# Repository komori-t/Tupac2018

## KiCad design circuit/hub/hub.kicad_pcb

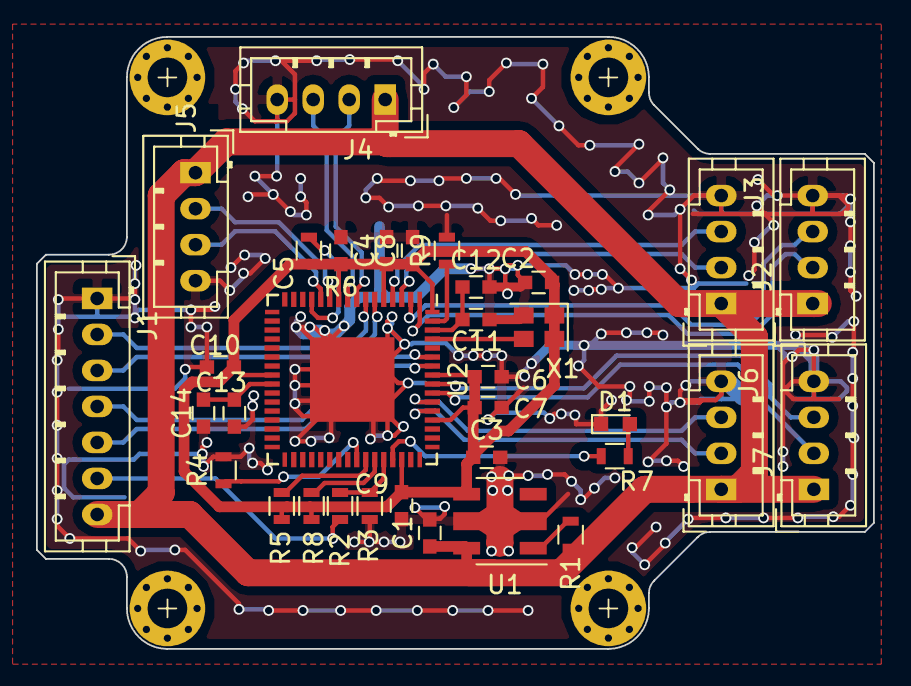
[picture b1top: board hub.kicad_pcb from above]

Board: 2 copper layers, 46.5 x 34.0 mm, 34 parts (0 on the bottom side), 32 nets.

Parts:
C1: 0.33u; C_0603
C2: 0.01u; C_0603
C3: 2.2u; C_0603
C4, C5, C6, C7, C8, C9, C10, C11, C13: 0.1u; C_0603
C12, C14: 1.0u; C_0603
D1: LED; LED_0603
J1: Host-IMU; JST_PH_B7B-PH-K_07x2.00mm_Straight
J2: Dev1; JST_PH_B4B-PH-K_04x2.00mm_Straight
J3: Dev2; JST_PH_B4B-PH-K_04x2.00mm_Straight
J4: Dev4; JST_PH_B4B-PH-K_04x2.00mm_Straight
J5: Dev5; JST_PH_B4B-PH-K_04x2.00mm_Straight
J6: Dev6; JST_PH_B4B-PH-K_04x2.00mm_Straight
J7: Dev7; JST_PH_B4B-PH-K_04x2.00mm_Straight
R1: 2k; R_0603
R2, R3, R4, R5, R6, R8: 100k; R_0603
R7: 1k; R_0603
R9: 12k; R_0603
U1: NJM2884U1-33; SOT-89-5_Housing
U2: USB2517; QFN-64-USB2517
X1: SG-210STF; Oscillator_SMD_SeikoEpson_SG210-4pin_2.5x2.0mm

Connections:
+3V3: C2.1, C3.1, C4.1, C5.1, C6.1, C7.1, C8.1, C9.1, C10.1, R5.2, R6.2, R8.2, U1.4, U2.5, U2.10, U2.24, U2.46, U2.52, U2.57, U2.64, X1.1, X1.4
+5V: C1.1, J1.7, J2.1, J3.1, J4.1, J5.1, J6.1, J7.1, R1.1, U1.5
/Clock: U2.61, X1.3
/Dev1D+: J2.3, U2.2
/Dev1D-: J2.2, U2.1
/Dev2D+: J3.3, U2.4
/Dev2D-: J3.2, U2.3
/Dev3D+: J1.2, U2.7
/Dev3D-: J1.3, U2.6
/Dev4D+: J4.3, U2.9
/Dev4D-: J4.2, U2.8
/Dev5D+: J5.3, U2.12
/Dev5D-: J5.2, U2.11
/Dev6D+: J6.3, U2.54
/Dev6D-: J6.2, U2.53
/Dev7D+: J7.3, U2.56
/Dev7D-: J7.2, U2.55
/HostD+: J1.4, U2.59
/HostD-: J1.5, U2.58
GND: C1.2, C2.2, C3.2, C4.2, C5.2, C6.2, C7.2, C8.2, C9.2, C10.2, C11.2, C12.2, C13.2, C14.2, D1.1, J1.1, J2.4, J3.4, J4.4, J5.4, J6.4, J7.4, R3.2, R4.2, R9.2, U1.2, U2.65, X1.2
unnamed: C11.1, C12.1, U2.62
unnamed: C13.1, C14.1, U2.25
unnamed: D1.2, R7.2
unnamed: R1.2, U1.1
unnamed: R2.2, R3.1, U2.44
unnamed: R4.1, U2.41
unnamed: R5.1, U2.42
unnamed: R6.1, U2.13
unnamed: R7.1, U2.45
unnamed: R8.1, U2.43
unnamed: R9.1, U2.63
VBUS: J1.6, R2.1

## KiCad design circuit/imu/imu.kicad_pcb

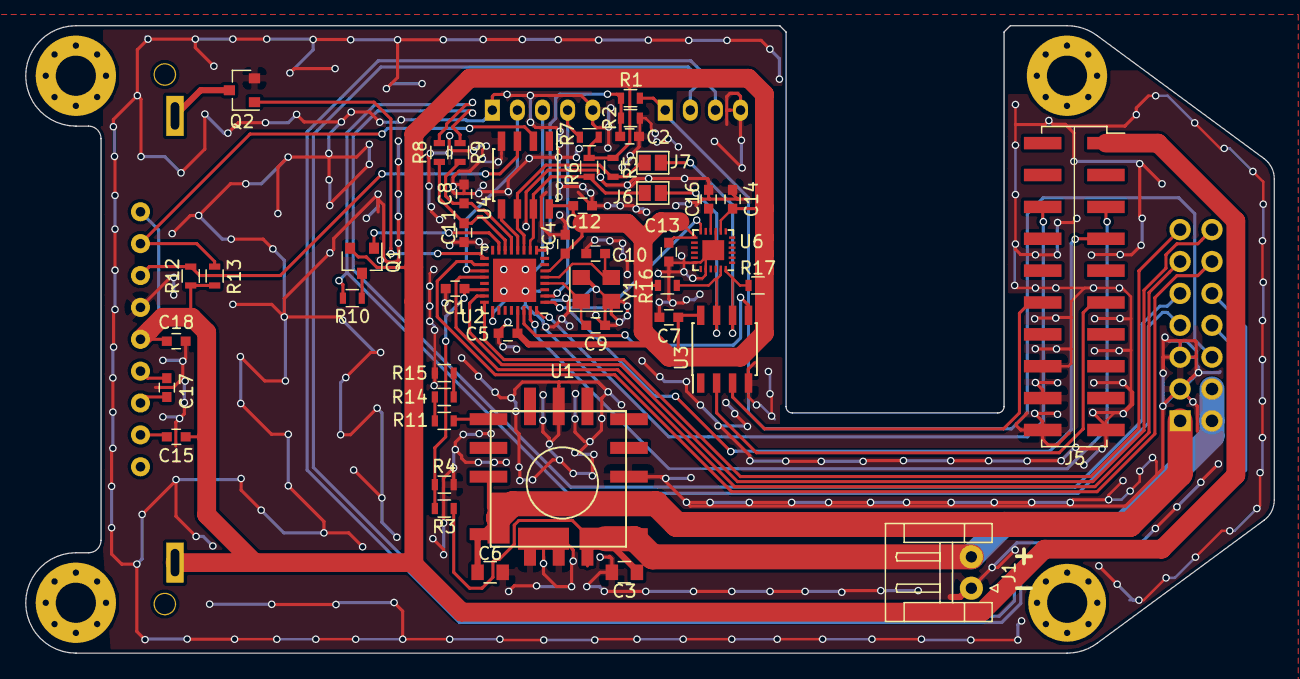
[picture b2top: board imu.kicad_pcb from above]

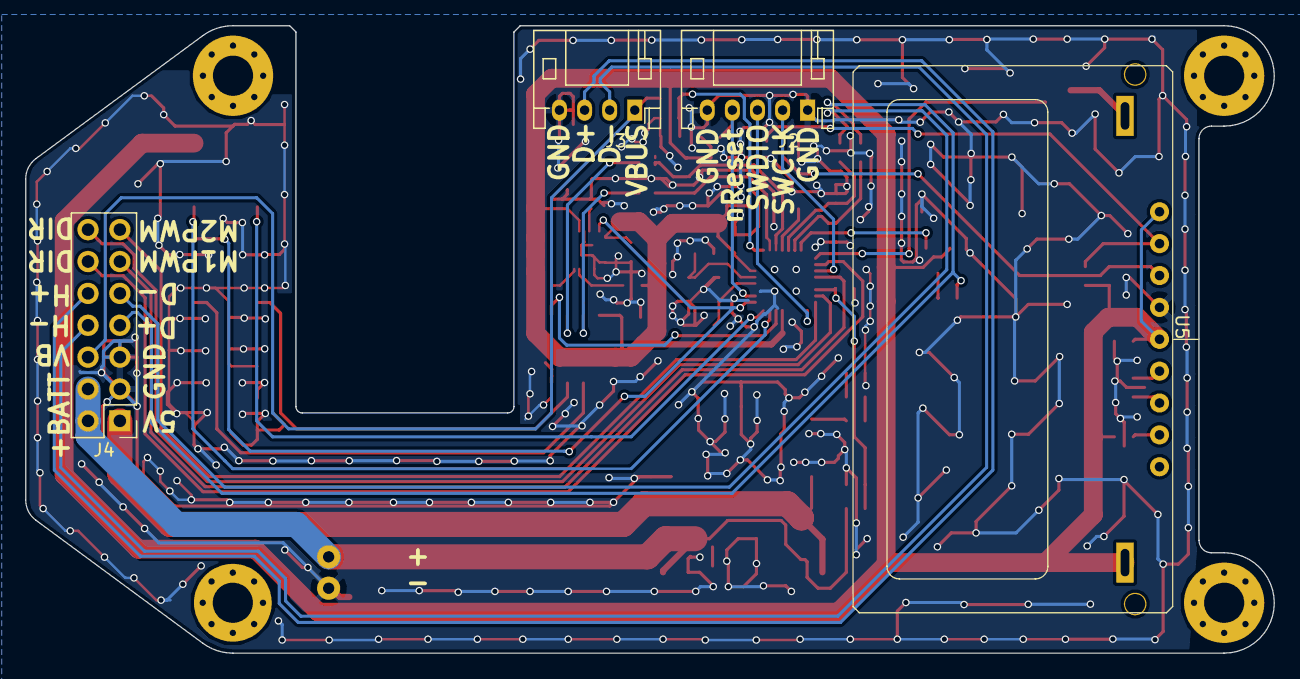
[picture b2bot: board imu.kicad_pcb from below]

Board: 2 copper layers, 99.5 x 50.0 mm, 51 parts (4 on the bottom side), 46 nets.

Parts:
C1, C2, C4, C5, C7, C12, C13, C16, C18: 0.1u; C_0603
C3: 22u; C_0805
C6: 10u; C_0805
C8, C9, C10, C11: 18p; C_0603
C14: 0.01u; C_0603
C15, C17: 1.0u; C_0603
J1: Batt; JST_EH_S02B-EH_02x2.50mm_Angled
J2: Debug; JST_PH_S5B-PH-K_05x2.00mm_Angled
J3: Jetson_USB; JST_PH_S4B-PH-K_04x2.00mm_Angled
J4: MIL-14; Pin_Header_Straight_2x07_Pitch2.54mm
J5: Jetson; Socket_Strip_Straight_2x10_Pitch2.54mm_SMD
J6, J7: GS2
Q1: Q_PMOS_GSD; SOT-23
Q2: Q_NMOS_GSD; SOT-23
R1, R2: 100k; R_0603
R3: 240k; R_0603
R4: 75k; R_0603
R5, R6, R16, R17: 4.7k; R_0603
R7, R12, R13: 10k; R_0603
R8, R9: 33; R_0603
R10: 1.5k; R_0603
R11: 1k; R_0603
R14: 330; R_0603
R15: 10; R_0603
U1: OKL-T/6-W12N-C; OKL-T_6-W12N-C
U2: LPC11U35FHI33/501; QFN-32-1EP_5x5mm_Pitch0.5mm
U3, U4: PCA9515A; SOIC-8_3.9x4.9mm_Pitch1.27mm
U5: AQM1602
U6: MPU6500; QFN-24-1EP_3x3mm_Pitch0.4mm
Y1: 12M; Crystal_SMD_SeikoEpson_FA238V-4pin_3.2x2.5mm

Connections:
+3V3: C4.1, C5.2, C7.1, C12.1, C13.1, C14.2, C15.1, C18.1, J5.1, Q1.2, R5.1, R6.1, R7.1, R12.1, R13.1, R16.1, R17.1, U2.6, U2.29, U3.8, U4.8, U5.5, U5.9, U5.10, U6.8, U6.13
+5V: C6.1, J4.1, U1.4, U1.5
+BATT: C3.1, J1.2, J4.2, J4.4, R3.1, U1.2
/11U35D+: C11.1, R8.2, U2.14
/11U35D-: C8.1, R9.2, U2.13
/ADC1: C1.1, R3.2, R4.1, U2.22
/ADC2/PWM9: J4.14, U2.23
/ADC3/PWM10: J4.13, U2.24
/D+: J4.7, R8.1, R10.2
/D-: J4.9, R9.1
/HostD+: J3.3, J4.10
/HostD-: J3.2, J4.8
/IMU_INT: J5.7, U2.1, U6.12
/IMU_SCL: J6.2, R16.2, U3.7, U6.23
/IMU_SDA: J7.2, R17.2, U3.6, U6.24
/JETSON_EN: U2.30, U3.5
/JETSON_RX1: J5.6, U2.32
/JETSON_SCL: J5.11, U3.2
/JETSON_SDA: J5.12, U3.3
/JETSON_TX1: J5.5, U2.31
/LCD_CONTRAST: Q2.1, U2.17
/LCD_EN: U2.12, U4.5
/M1DIR: J4.12, U2.18
/M1PWM: J4.11, U2.20
/MCU_SCL: J6.1, R6.2, U2.10, U4.7
/MCU_SDA: J7.1, R5.2, U2.11, U4.6
/SWCLK: J2.2, U2.19
/SWDIO: J2.3, U2.25
/VBUS_DET: C2.1, R1.2, R2.1, U2.9
/~MCU_RESET: J2.4, R7.2, U2.2
/~USB_CONNECT: Q1.1, U2.15
GND: C1.2, C2.2, C3.2, C4.2, C5.1, C6.2, C7.2, C8.2, C9.1, C10.1, C11.2, C12.2, C13.2, C14.1, C16.2, C18.2, J1.1, J2.1, J2.5, J3.4, J4.3, J4.5, J5.16, J5.18, J5.19, J5.20, Q2.2, R2.2, R4.2, R15.2, U1.1, U1.3, U1.7, U2.33, U3.4, U4.4, U5.6, U6.9, U6.18, U6.20, U6.25, Y1.2, Y1.4
unnamed: C9.2, U2.4, Y1.1
unnamed: C10.2, U2.5, Y1.3
unnamed: C15.2, U5.2
unnamed: C16.1, U6.10
unnamed: C17.1, U5.3
unnamed: C17.2, U5.4
unnamed: Q1.3, R10.1
unnamed: Q2.3, U5.11
unnamed: R11.1, R14.1
unnamed: R11.2, U1.6
unnamed: R12.2, U4.3, U5.7
unnamed: R13.2, U4.2, U5.8
unnamed: R14.2, R15.1
VBUS: J3.1, J4.6, R1.1

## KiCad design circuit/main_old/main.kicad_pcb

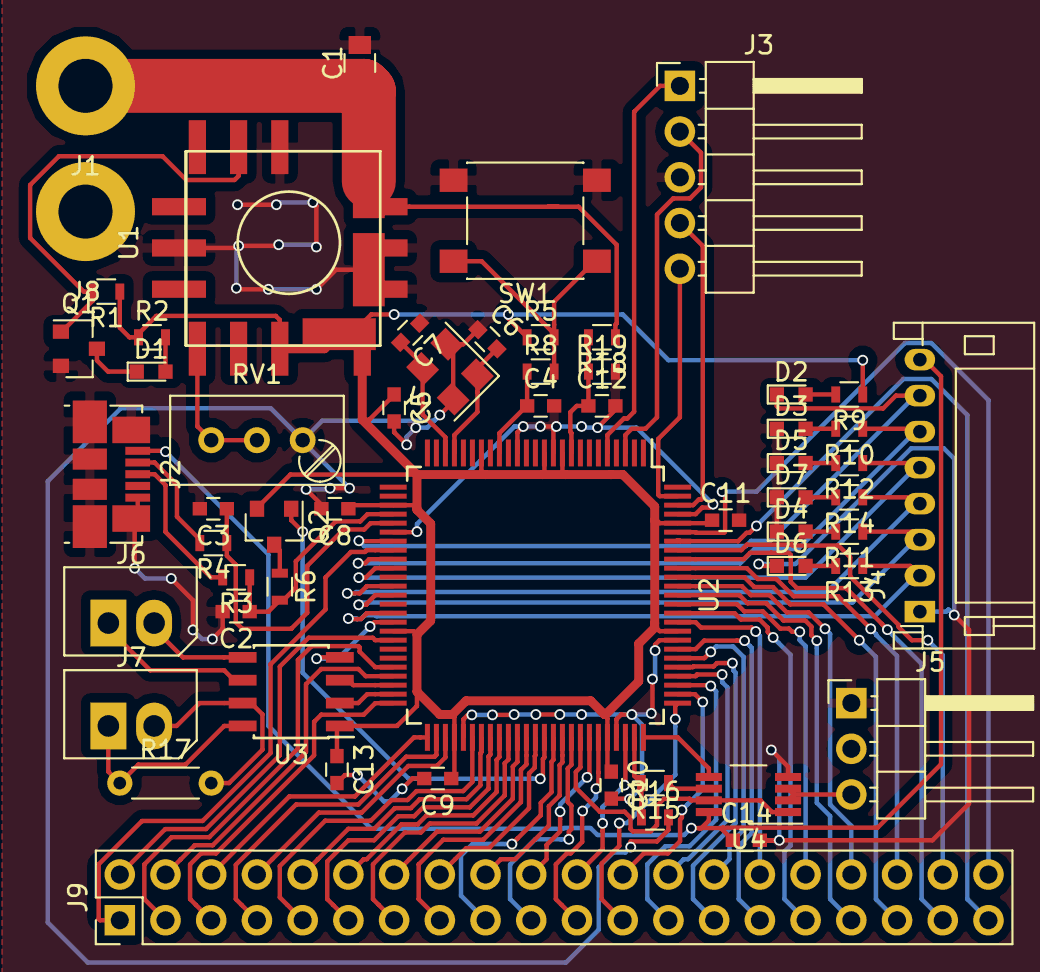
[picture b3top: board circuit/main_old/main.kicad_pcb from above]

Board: 2 copper layers, 57 parts (0 on the bottom side), 86 nets.

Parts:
C1: 22u; C_0805
C2, C3: 18p; C_0603
C4, C8, C9, C10, C11, C12, C13, C14: 0.1u; C_0603
C5: 10u; C_0603
C6, C7: 10p; C_0603
D1, D2, D3, D4, D5, D6, D7: LED; LED_0603
J1: Batt+; Wire_Pad_5.5
J2: USB_B_Micro; USB_Micro-B_Molex_47346-0001
J3: Debugger; Pin_Header_Angled_1x05_Pitch2.54mm
J4: LED; JST_PH_S8B-PH-K_08x2.00mm_Angled
J5: Futaba; Pin_Header_Angled_1x03_Pitch2.54mm
J6: MD; Molex_SPOX-5267_22-03-5025_02x2.54mm_Straight
J7: IMU; Molex_SPOX-5267_22-03-5025_02x2.54mm_Straight
J8: Batt-; Wire_Pad_5.5
J9: Expansion; Pin_Header_Straight_2x20_Pitch2.54mm
Q1: Q_NMOS_GSD; SOT-23
Q2: Q_PMOS_GSD; SOT-23
R1: 100k; R_0603
R2, R9, R10, R11, R12, R13, R14, R15: 1k; R_0603
R3, R4: 33; R_0603
R5: 10k; R_0603
R6: 1.5k; R_0603
R8, R16: 2k; R_0603
R17: 120; R_Axial_DIN0204_L3.6mm_D1.6mm_P5.08mm_Horizontal
R18: 2.4k; R_0603
R19: 750; R_0603
RV1: POT; Potentiometer_Trimmer_Bourns_3296W
SW1: SW_Push; SW_SPST_PTS645
U1: OKL-T/6-W12N-C; OKL-T_6-W12N-C
U2: LPC1768FBD100; LQFP-100_14x14mm_Pitch0.5mm
U3: RS485Transceiver; SOIC-8_3.9x4.9mm_Pitch1.27mm
U4: 74LVC2G241; VSSOP-8_3.0x3.0mm_Pitch0.65mm
Y1: Crystal_GND24; Crystal_SMD_SeikoEpson_FA238V-4pin_3.2x2.5mm

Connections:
+3V3: C5.1, C8.1, C9.1, C10.1, C11.1, C13.1, Q2.2, R1.1, R2.1, R5.1, R9.1, U1.4, U1.5, U2.10, U2.12, U2.19, U2.28, U2.42, U2.54, U2.71, U2.84, U2.96, U3.1
+5V: C14.1, J2.1, J4.8, U4.8
+BATT: C1.1, J1.1, R18.1, U1.2
ADC: C12.1, R18.2, R19.1, U2.9
D+: C2.1, R3.1, R6.2, U2.29
D-: C3.1, R4.1, U2.30
DTR1: U2.68, U4.1, U4.7
Exp1: J9.1, U2.33
Exp2: J9.2, U2.43
Exp3: J9.3, U2.46
Exp4: J9.4, U2.47
Exp5: J9.5, U2.50
Exp6: J9.6, U2.51
Exp7: J9.7, U2.52
Exp8: J9.8, U2.53
Exp9: J9.9, U2.56
Exp10: J9.10, U2.57
Exp11: J9.11, U2.58
Exp12: J9.12, U2.59
Exp13: J9.13, U2.60
Exp14: J9.14, U2.61
Exp15: J9.15, U2.62
Exp16: J9.16, U2.63
Exp17: J9.17, U2.65
Exp18: J9.18, U2.66
Exp19: J9.19, U2.67
Exp20: J9.20, U2.69
Exp21: J9.21, U2.70
Exp22: J9.22, U2.73
Exp23: J9.23, U2.76
Exp24: J9.24, U2.77
Exp25: J9.25, U2.78
Exp26: J9.26, U2.79
Exp27: J9.27, U2.80
Exp28: J9.28, U2.81
Exp29: J9.29, U2.82
Exp30: J9.30, U2.85
Exp31: J9.31, U2.86
Exp32: J9.32, U2.87
Exp33: J9.33, U2.88
Exp34: J9.34, U2.89
Exp35: J9.35, U2.90
Exp36: J9.36, U2.91
Exp37: J9.37, U2.92
Exp38: J9.38, U2.93
Exp39: J9.39, U2.94
Exp40: J9.40, U2.95
GND: C1.2, C2.2, C3.2, C4.2, C5.2, C6.1, C7.1, C8.2, C9.2, C10.2, C11.2, C12.2, C13.2, C14.2, D3.1, D4.1, D5.1, D6.1, D7.1, J2.5, J2.6, J3.3, J4.1, J5.1, J8.1, Q1.2, R16.2, R19.2, RV1.1, SW1.2, U1.1, U1.3, U1.7, U2.11, U2.15, U2.31, U2.41, U2.55, U2.72, U2.83, U2.97, U3.4, U4.4, Y1.2, Y1.4
unnamed: C6.2, U2.22, Y1.1
unnamed: C7.2, U2.23, Y1.3
unnamed: D1.1, Q1.3
unnamed: D1.2, R2.2
unnamed: D2.2, R9.2
unnamed: D3.2, R10.2
unnamed: D4.2, R11.2
unnamed: D5.2, R12.2
unnamed: D6.2, R13.2
unnamed: D7.2, R14.2
unnamed: J2.2, R4.2
unnamed: J2.3, R3.2
unnamed: J5.3, U4.2, U4.3
unnamed: J6.1, U3.6
unnamed: J6.2, U3.5
unnamed: J7.1, R17.1, U3.8
unnamed: J7.2, R17.2, U3.7
unnamed: Q2.3, R6.1
unnamed: R5.2, R8.2, SW1.1
unnamed: R15.1, U4.6
unnamed: RV1.2, RV1.3, U1.6
PGOOD: Q1.1, R1.2, U1.10
PWM1: D2.1, J4.7, U2.32
PWM2: J4.6, R10.1, U2.34
PWM3: J4.5, R12.1, U2.35
PWM4: J4.4, R14.1, U2.37
PWM5: J4.3, R11.1, U2.38
PWM6: J4.2, R13.1, U2.40
RX0: J3.5, U2.99
RX1: R15.2, R16.1, U2.74
RX2: U2.49, U3.2
SWCLK: J3.1, U2.5
SWDIO: J3.2, U2.3
TX0: J3.4, U2.98
TX1: U2.75, U4.5
TX2: U2.48, U3.3
USB_Connect: Q2.1, U2.64
~RESET: C4.1, R8.1, U2.17

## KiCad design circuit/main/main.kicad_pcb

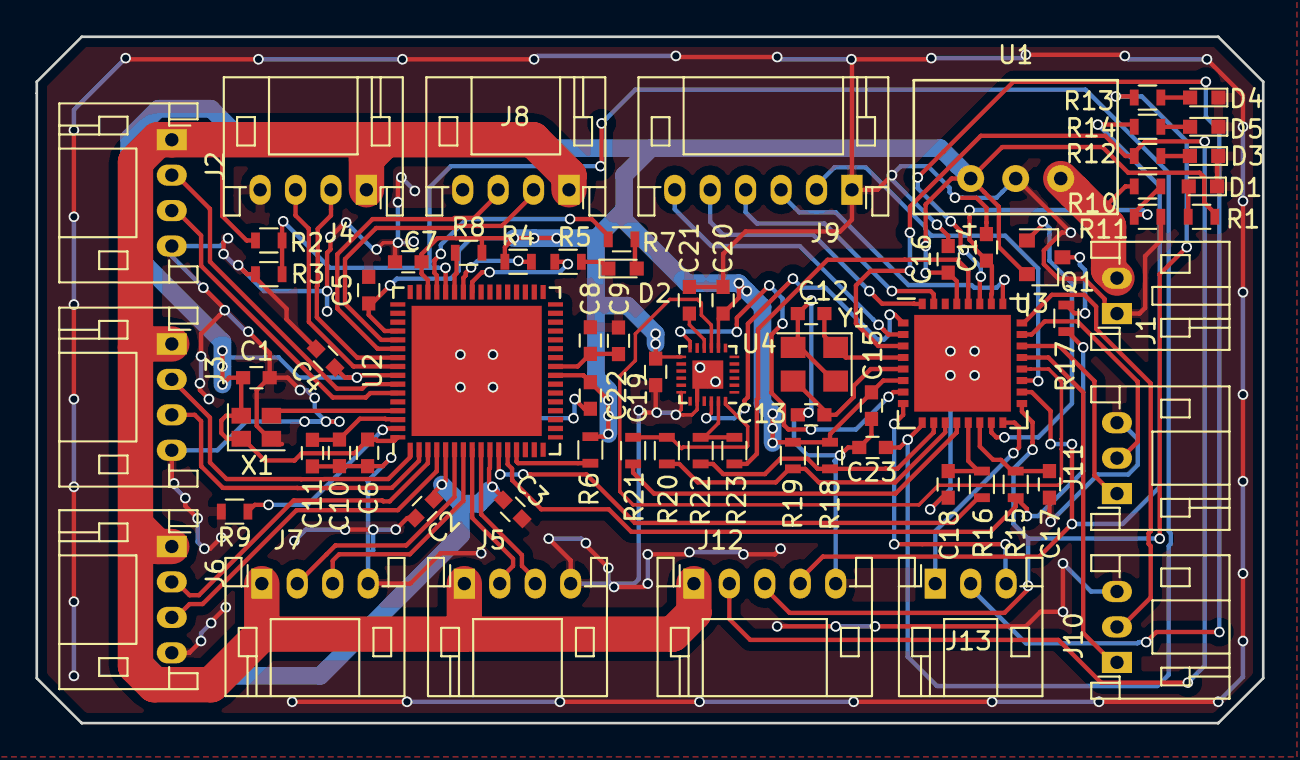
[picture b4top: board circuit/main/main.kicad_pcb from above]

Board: 2 copper layers, 69.2 x 38.7 mm, 71 parts (0 on the bottom side), 67 nets.

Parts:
C1, C20: 0.01u; C_0603
C2, C3, C4, C5, C6, C7, C8, C10, C14, C15, C16, C19, C21, C22, C23: 0.1u; C_0603
C9, C11: 1.0u; C_0603
C12, C13, C17, C18: 18p; C_0603
D1, D2, D3, D4, D5: LED; LED_0603
J1: Batt; JST_PH_S2B-PH-K_02x2.00mm_Angled
J2: Jetson; JST_PH_S4B-PH-K_04x2.00mm_Angled
J3: U2D2; JST_PH_S4B-PH-K_04x2.00mm_Angled
J4: FLIR; JST_PH_S4B-PH-K_04x2.00mm_Angled
J5: Speaker; JST_PH_S4B-PH-K_04x2.00mm_Angled
J6: WebCam; JST_PH_S4B-PH-K_04x2.00mm_Angled
J7: Microphone; JST_PH_S4B-PH-K_04x2.00mm_Angled
J8: USB7; JST_PH_S4B-PH-K_04x2.00mm_Angled
J9: Debug; JST_PH_S6B-PH-K_06x2.00mm_Angled
J10: Motor1; JST_PH_S3B-PH-K_03x2.00mm_Angled
J11: Motor2; JST_PH_S3B-PH-K_03x2.00mm_Angled
J12: PWM; JST_PH_S5B-PH-K_05x2.00mm_Angled
J13: EXP; JST_PH_S3B-PH-K_03x2.00mm_Angled
Q1: Q_PMOS_GSD; SOT-23
R1, R7, R12, R13, R14: 1k; R_0603
R2, R3, R4, R5, R6, R8: 100k; R_0603
R9: 12k; R_0603
R10: 240k; R_0603
R11: 75k; R_0603
R15, R16: 33; R_0603
R17: 1.5k; R_0603
R18, R19: 2.2k; R_0603
R20, R21, R22, R23: 0; R_0603
U1: M78A
U2: USB2517; QFN-64-1EP_9x9mm_Pitch0.5mm
U3: LPC11U35FHI33/501; QFN-32-1EP_7x7mm_Pitch0.65mm
U4: MPU6500; QFN-24-1EP_3x3mm_Pitch0.4mm
X1: SG-210STF_24MHz; Oscillator_SMD_SeikoEpson_SG210-4pin_2.5x2.0mm
Y1: 12M; Oscillator_SMD_SeikoEpson_SG8002CE-4pin_3.2x2.5mm

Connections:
2.5V: C23.1, R2.2, R3.1, U2.44, U3.9
+3V3: C1.1, C2.1, C3.1, C4.1, C5.1, C6.1, C7.1, C15.1, C16.1, C19.1, C20.1, C22.1, Q1.2, R1.1, R4.1, R6.1, R8.2, R18.1, R19.1, U1.3, U2.5, U2.10, U2.24, U2.46, U2.52, U2.57, U2.64, U3.6, U3.29, U4.8, U4.13, X1.1, X1.4
+5V: J2.1, J3.1, J4.1, J5.1, J6.1, J7.1, J8.1, J12.1, R2.1
+BATT: J1.2, R10.1, U1.1
/Hub/CFG_SEL0: R5.1, U2.41
/Hub/CFG_SEL1: R4.2, U2.42
/Hub/CFG_SEL2: R6.2, U2.13
/Hub/HostD+: J2.3, U2.59
/Hub/HostD-: J2.2, U2.58
/Hub/Hub_Clock: U2.61, X1.3
/Hub/SUSP_IND: R7.1, U2.45
/Hub/USB1D+: J4.3, U2.56
/Hub/USB1D-: J4.2, U2.55
/Hub/USB2D+: J8.3, U2.54
/Hub/USB2D-: J8.2, U2.53
/Hub/USB4D+: J5.3, U2.9
/Hub/USB4D-: J5.2, U2.8
/Hub/USB5D+: J7.3, U2.7
/Hub/USB5D-: J7.2, U2.6
/Hub/USB6D+: J6.3, U2.4
/Hub/USB6D-: J6.2, U2.3
/Hub/USB7D+: J3.3, U2.2
/Hub/USB7D-: J3.2, U2.1
/Hub/VDD18: C8.1, C9.1, U2.25
/Hub/VDD18PLL: C10.1, C11.1, U2.62
/MCU/11U35D+: C17.1, R15.2, U3.14
/MCU/11U35D-: C18.1, R16.2, U3.13
/MCU/6500INT: U3.7, U4.12
/MCU/ADC5: C14.1, R10.2, R11.1, U3.26
/MCU/EXP1: J13.1, U3.16
/MCU/EXP2: J13.2, U3.27
/MCU/EXP3: J13.3, U3.8
/MCU/EXPWM1: J12.2, R12.1, U3.3
/MCU/EXPWM2: J12.3, R13.1, U3.17
/MCU/EXPWM3: J12.4, R14.1, U3.18
/MCU/MCUD+: R15.1, R17.2, U2.12
/MCU/MCUD-: R16.1, U2.11
/MCU/MCU_RX: J9.4, U3.31
/MCU/MCU_TX: J9.5, U3.32
/MCU/MISO1: U3.20, U4.9
/MCU/MOSI1: R21.2, U3.12
/MCU/Motor1_Dir: J10.1, U3.21
/MCU/Motor1_PWM: J10.2, U3.24
/MCU/Motor2_Dir: J11.1, U3.22
/MCU/Motor2_PWM: J11.2, U3.23
/MCU/SCK1: R23.2, U3.28
/MCU/SCL: R18.2, R22.2, U3.10
/MCU/SDA: R19.2, R20.2, U3.11
/MCU/SWCLK: J9.2, U3.19
/MCU/SWDIO: J9.3, U3.25
/MCU/XTALIN: C12.1, U3.4, Y1.1
/MCU/XTALOUT: C13.1, U3.5, Y1.3
/MCU/~MCU_Reset: J9.6, U3.2
/MCU/~SS1: U3.1, U4.22
/MCU/~USB_CONNECT: Q1.1, U3.15
GND: C1.2, C2.2, C3.2, C4.2, C5.2, C6.2, C7.2, C8.2, C9.2, C10.2, C11.2, C12.2, C13.2, C14.2, C15.2, C16.2, C17.2, C18.2, C19.2, C20.2, C21.2, C22.2, C23.2, D1.1, D2.1, D3.1, D4.1, D5.1, J1.1, J2.4, J3.4, J4.4, J5.4, J6.4, J7.4, J8.4, J9.1, J10.3, J11.3, J12.5, R3.2, R5.2, R9.2, R11.2, U1.2, U2.65, U3.33, U4.18, U4.20, U4.25, X1.2, Y1.2, Y1.4
unnamed: C21.1, U4.10
unnamed: D1.2, R1.2
unnamed: D2.2, R7.2
unnamed: D3.2, R12.2
unnamed: D4.2, R13.2
unnamed: D5.2, R14.2
unnamed: Q1.3, R17.1
unnamed: R8.1, U2.43
unnamed: R9.1, U2.63
unnamed: R20.1, R21.1, U4.24
unnamed: R22.1, R23.1, U4.23

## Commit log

2018-01-15 add serial
2018-03-11 add circuit
2018-03-11 add futaba serial servo library
2018-03-11 add Dynamixel library
2018-03-15 Add TDM
2018-03-16 change title add advices
2018-03-16 Size of Robotだけ英訳した
2018-03-16 siunitx使った つかれた
2018-03-16 つかれた
2018-03-16 Locomotion strategyを英訳
2018-03-16 全部英訳
2018-03-17 finalize TDM
2018-03-18 add team record, change leader's name, change abstract
2018-03-20 Create static servo library and dynamic servo config application
2018-03-21 Fix bug in Serial::transfer Enable timeout Report more error details
2018-03-21 Capitalize
2018-03-21 Fix compiler warning Fix position calculation
2018-03-21 Fix compiler warning
2018-03-21 Fix wrong rvalue reference usage
2018-03-21 Remove outdated files
2018-04-12 add hub, imu
2018-05-13 do not ignore .lib for KiCAD libraries
2018-05-13 Static servo classes won't be compiled due to clang bug
2018-05-13 add sysfs-mbed
2018-05-13 add ServoController
2018-05-14 Prepare servo converter
2018-05-14 Limp on terminate
2018-05-22 add comments
2018-06-08 add Controller, Robot
2018-06-12 Support changing ID
2018-06-12 Support broadcast
2018-06-12 Support broadcasting Delete Transport class Fix shutdown
2018-06-12 update circuits
2018-06-12 fix i2c driver
2018-06-12 create DMP_Tegra
2018-06-12 create Makefile pass variable address to gstreamer (experimental)
2018-06-13 change GUI add timer
2018-06-13 support dynamixel led add servos
2018-06-15 implement servo visualizations implement acknowledge
2018-06-21 voice task commands
2018-06-21 additional servo test commands
2018-06-21 make angle 32bits
2018-06-21 add voltage reader feature automatic camera index detection over current shutdown servo reboot
2018-06-21 QR code reader
2018-06-21 motion detector and streamer
2018-06-21 add launcher
2018-06-21 hazmat detection
2018-06-21 file replacement
2018-06-21 presets, feedbacks, and more
2018-06-21 file deletion
